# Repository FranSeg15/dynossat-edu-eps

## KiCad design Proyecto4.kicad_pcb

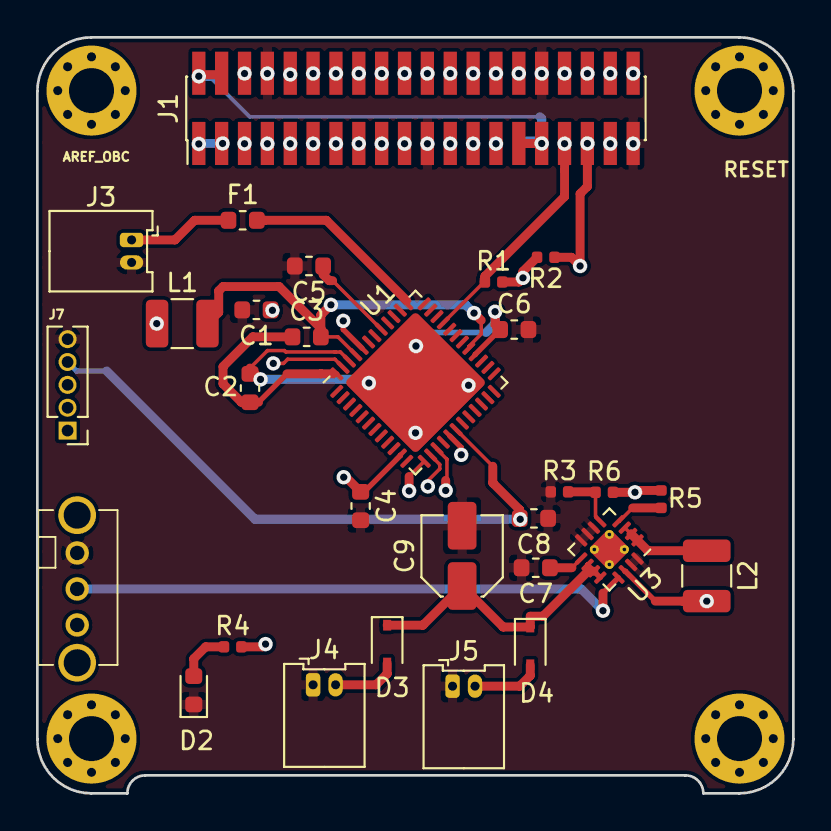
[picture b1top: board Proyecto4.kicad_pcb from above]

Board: 4 copper layers, 42.0 x 42.0 mm, 30 parts (1 on the bottom side), 51 nets.

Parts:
C1, C4: 4.9uF; C_0603_1608Metric
C2, C6: 4.7uF; C_0603_1608Metric
C3: 470nF; C_0603_1608Metric
C5: 1.01uF; C_0603_1608Metric
C7: 3.3nF; C_0603_1608Metric
C8: 0.1uF; C_0603_1608Metric
C9: 10uF; C_Elec_4x5.4
D2: LED_Small; LED_0603_1608Metric
D3, D4: D_Schottky_Small; D_SOD-323
F1: Fuse_3A; Fuse_0603_1608Metric
J1: Conn_02x20_Odd_Even; PinHeader_2x20_P1.27mm_Vertical_SMD
J2: Conn_02x20_Odd_Even; PinSocket_2x20_P1.27mm_Vertical_SMD
J3: Battery; Molex_PicoBlade_53048-0210_1x02_P1.25mm_Horizontal
J4: PV Panel 2; Molex_PicoBlade_53048-0210_1x02_P1.25mm_Horizontal
J5: PV Panel 1; Molex_PicoBlade_53048-0210_1x02_P1.25mm_Horizontal
J7: Conn_01x05_Female; PinHeader_1x05_P1.27mm_Vertical
L1: 15uH; L_1210_3225Metric
L2: 2.2uH; L_1210_3225Metric
R1, R2: 47k; R_0402_1005Metric
R3: 10k; R_0402_1005Metric
R4: 330R; R_0402_1005Metric
R5: 100k; R_0402_1005Metric
R6: 31.2K; R_0402_1005Metric
SW2: SW_SPDT; OS102011MA1QN1
U1: STM32WL55CC; QFN-48-1EP_7x7mm_P0.5mm_EP5.6x5.6mm
U3: TPS62152; VQFN-16-1EP_3x3mm_P0.5mm_EP1.68x1.68mm_ThermalVias

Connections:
+3V3_EPS: C1.1, C4.1, J7.1, L2.2, R1.2, R2.2, R4.2, R5.2, R6.2, U1.11, U1.44, U3.14
+3V3_SAT: J1.2, J1.4, J1.29, J1.31, J2.2, J2.4, J2.29, J2.31
+5V_SAT: J1.1, J1.3, J2.1, J2.3
+BATT: F1.2, U1.37
/Connectors/A0_OBC: J1.10, J2.10
/Connectors/A1_OBC: J1.12, J2.12
/Connectors/A2_OBC: J1.14, J2.14
/Connectors/A3_OBC: J1.16, J2.16
/Connectors/A4_OBC: J1.18, J2.18
/Connectors/A5_OBC: J1.20, J2.20
/Connectors/D0_OBC: J1.9, J2.9
/Connectors/D1_OBC: J1.11, J2.11
/Connectors/D2_OBC: J1.13, J2.13
/Connectors/D3_OBC: J1.15, J2.15
/Connectors/D4_OBC: J1.17, J2.17
/Connectors/D5_OBC: J1.19, J2.19
/Connectors/D6_OBC: J1.23, J2.23
/Connectors/D7_OBC: J1.25, J2.25
/Connectors/D8_OBC: J1.27, J2.27
/Connectors/D9_OBC: J1.37, J2.37
/Connectors/OBC_SWDCLK: J1.38, J2.38
/Connectors/OBC_SWDIO: J1.40, J2.40
AREF_SAT: J1.6, J2.6
EPS_PWR_EN: SW2.2, U3.13
EPS_nRST: C8.2, J7.4, U1.18
GND: C1.2, C4.2, C5.2, C6.2, C7.2, C8.1, C9.2, D2.1, J1.8, J1.21, J1.32, J1.39, J2.8, J2.21, J2.32, J2.39, J3.2, J4.1, J5.1, J7.5, R3.1, SW2.1, U1.49, U3.6, U3.7, U3.8, U3.15, U3.16
I2C_BUS_SCL: J1.35, J2.35, R2.1, U1.17
I2C_BUS_SDA: J1.33, J2.33, R1.1, U1.33
INT_IMU_OBC: J1.7, J2.7
unnamed: C2.2, C3.1, U1.48
unnamed: C5.1, U1.41
unnamed: C7.1, U3.9
unnamed: D2.2, R4.1
unnamed: D3.2, J4.2
unnamed: D4.2, J5.2
unnamed: F1.1, J3.1
unnamed: L1.1, U1.47
unnamed: L2.1, U3.1, U3.2, U3.3
unnamed: R3.2, R6.1, U3.5
unnamed: R5.1, U3.4
OBC_OVTEMP: J1.34, J2.34
OBC_RX: J1.30, J2.30
OBC_TX: J1.28, J2.28
PV: C9.1, D3.1, D4.1, U3.10, U3.11, U3.12
SAT_PWR_EN: J1.5, J2.5
SAT_nRST: J1.36, J2.36
SPI_BUS_SCK: J1.24, J2.24, U1.13
SPI_BUS_SDI: J1.26, J2.26, U1.15
SPI_BUS_SDO: J1.22, J2.22, U1.14
VDDRFF1-45: C3.2, L1.2, U1.29, U1.45
VDDSMPS-VDDRF: C2.1, C6.1, U1.28, U1.46

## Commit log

2020-11-27 Final
